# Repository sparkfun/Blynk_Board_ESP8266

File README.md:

SparkFun Blynk Board - ESP8266
========================================

[*SparkFun Blynk Board - ESP8266 (WRL-13794)*](https://www.sparkfun.com/products/13794)

The SparkFun Blynk Board is specially designed to work with the [Blynk mobile app](http://blynk.cc), for iOS or Android devices. Combining the Blynk Board with the Blynk app, you'll be able to easily complete a variety of Internet-of-Things (IoT) based projects: control LEDs from your phone! Wire up a door switch and receive phone notifications when it opens or closes. Plug a soil moisture sensor into a plant, and have it tweet at you when it's thirsty!

All of these projects - and more! - are pre-loaded into the Blynk Board. All you have to do is provision it (using the Blynk app), and start tinkering!

Repository Contents
-------------------

* **/Firmware** - Blynk Board core firmware and example code.
* **/Hardware** - Eagle design files (.brd, .sch)
* **/Production** - Production panel files (.brd)

Documentation
--------------
* **[Getting Started Guide](https://learn.sparkfun.com/tutorials/getting-started-with-the-sparkfun-blynk-board)** - Learn how to connect your Blynk Board to Wi-Fi, and start Blynking!
* **[Blynk Board Project Guide](https://learn.sparkfun.com/tutorials/blynk-board-project-guide/introduction)** - Explore over a dozen Blynk projects pre-loaded into the Blynk Board.
* **[Blynk Board Arduino Development Guide](https://learn.sparkfun.com/tutorials/blynk-board-arduino-development-guide)** - Learn how to begin programming the Blynk Board using Arduino, so you can create projects of your own!
* **[SparkFun Graphical Datasheets](https://github.com/sparkfun/Graphical_Datasheets/tree/master/Datasheets/ESP8266/BlynkBoard)** -Graphical Datasheets for the SparkFun Blynk Board.

Product Versions
----------------
* [SparkFun Blynk Board - ESP8266 (v1.0) (WRL-13794)](https://www.sparkfun.com/products/13794)- Initial release of the SparkFun Blynk Board - ESP8266.
* IoT Starter Kit with Blynk Board
  * [(KIT-14682)](https://www.sparkfun.com/products/14682) - Updated parts kit with thicker resistor leads.
  * [(KIT-13865)](https://www.sparkfun.com/products/13865) - A parts kit including the SparkFun Blynk Board.

Version History
---------------
* [HW v1.0, FW v1.0.3](https://github.com/sparkfun/Blynk_Board_ESP8266/releases/tag/HW_v1.0-FW_v1.0.3) - Minor update for ESP8266 Community board add on (v2.6.0 and above) when using interrupts.
* [HW v1.0, FW v1.0.2](https://github.com/sparkfun/Blynk_Board_ESP8266/releases/tag/HW_v1.0-FW_v1.0.2) - Initial release of the SparkFun Blynk Board hardware and firmware.

License Information
-------------------

This product is _**open source**_! 

Please review the LICENSE.md file for license information. 

If you have any questions or concerns on licensing, please contact technical support on our [SparkFun forums](https://forum.sparkfun.com/viewforum.php?f=152).

Distributed as-is; no warranty is given.

- Your friends at SparkFun.

_<COLLABORATION CREDIT>_

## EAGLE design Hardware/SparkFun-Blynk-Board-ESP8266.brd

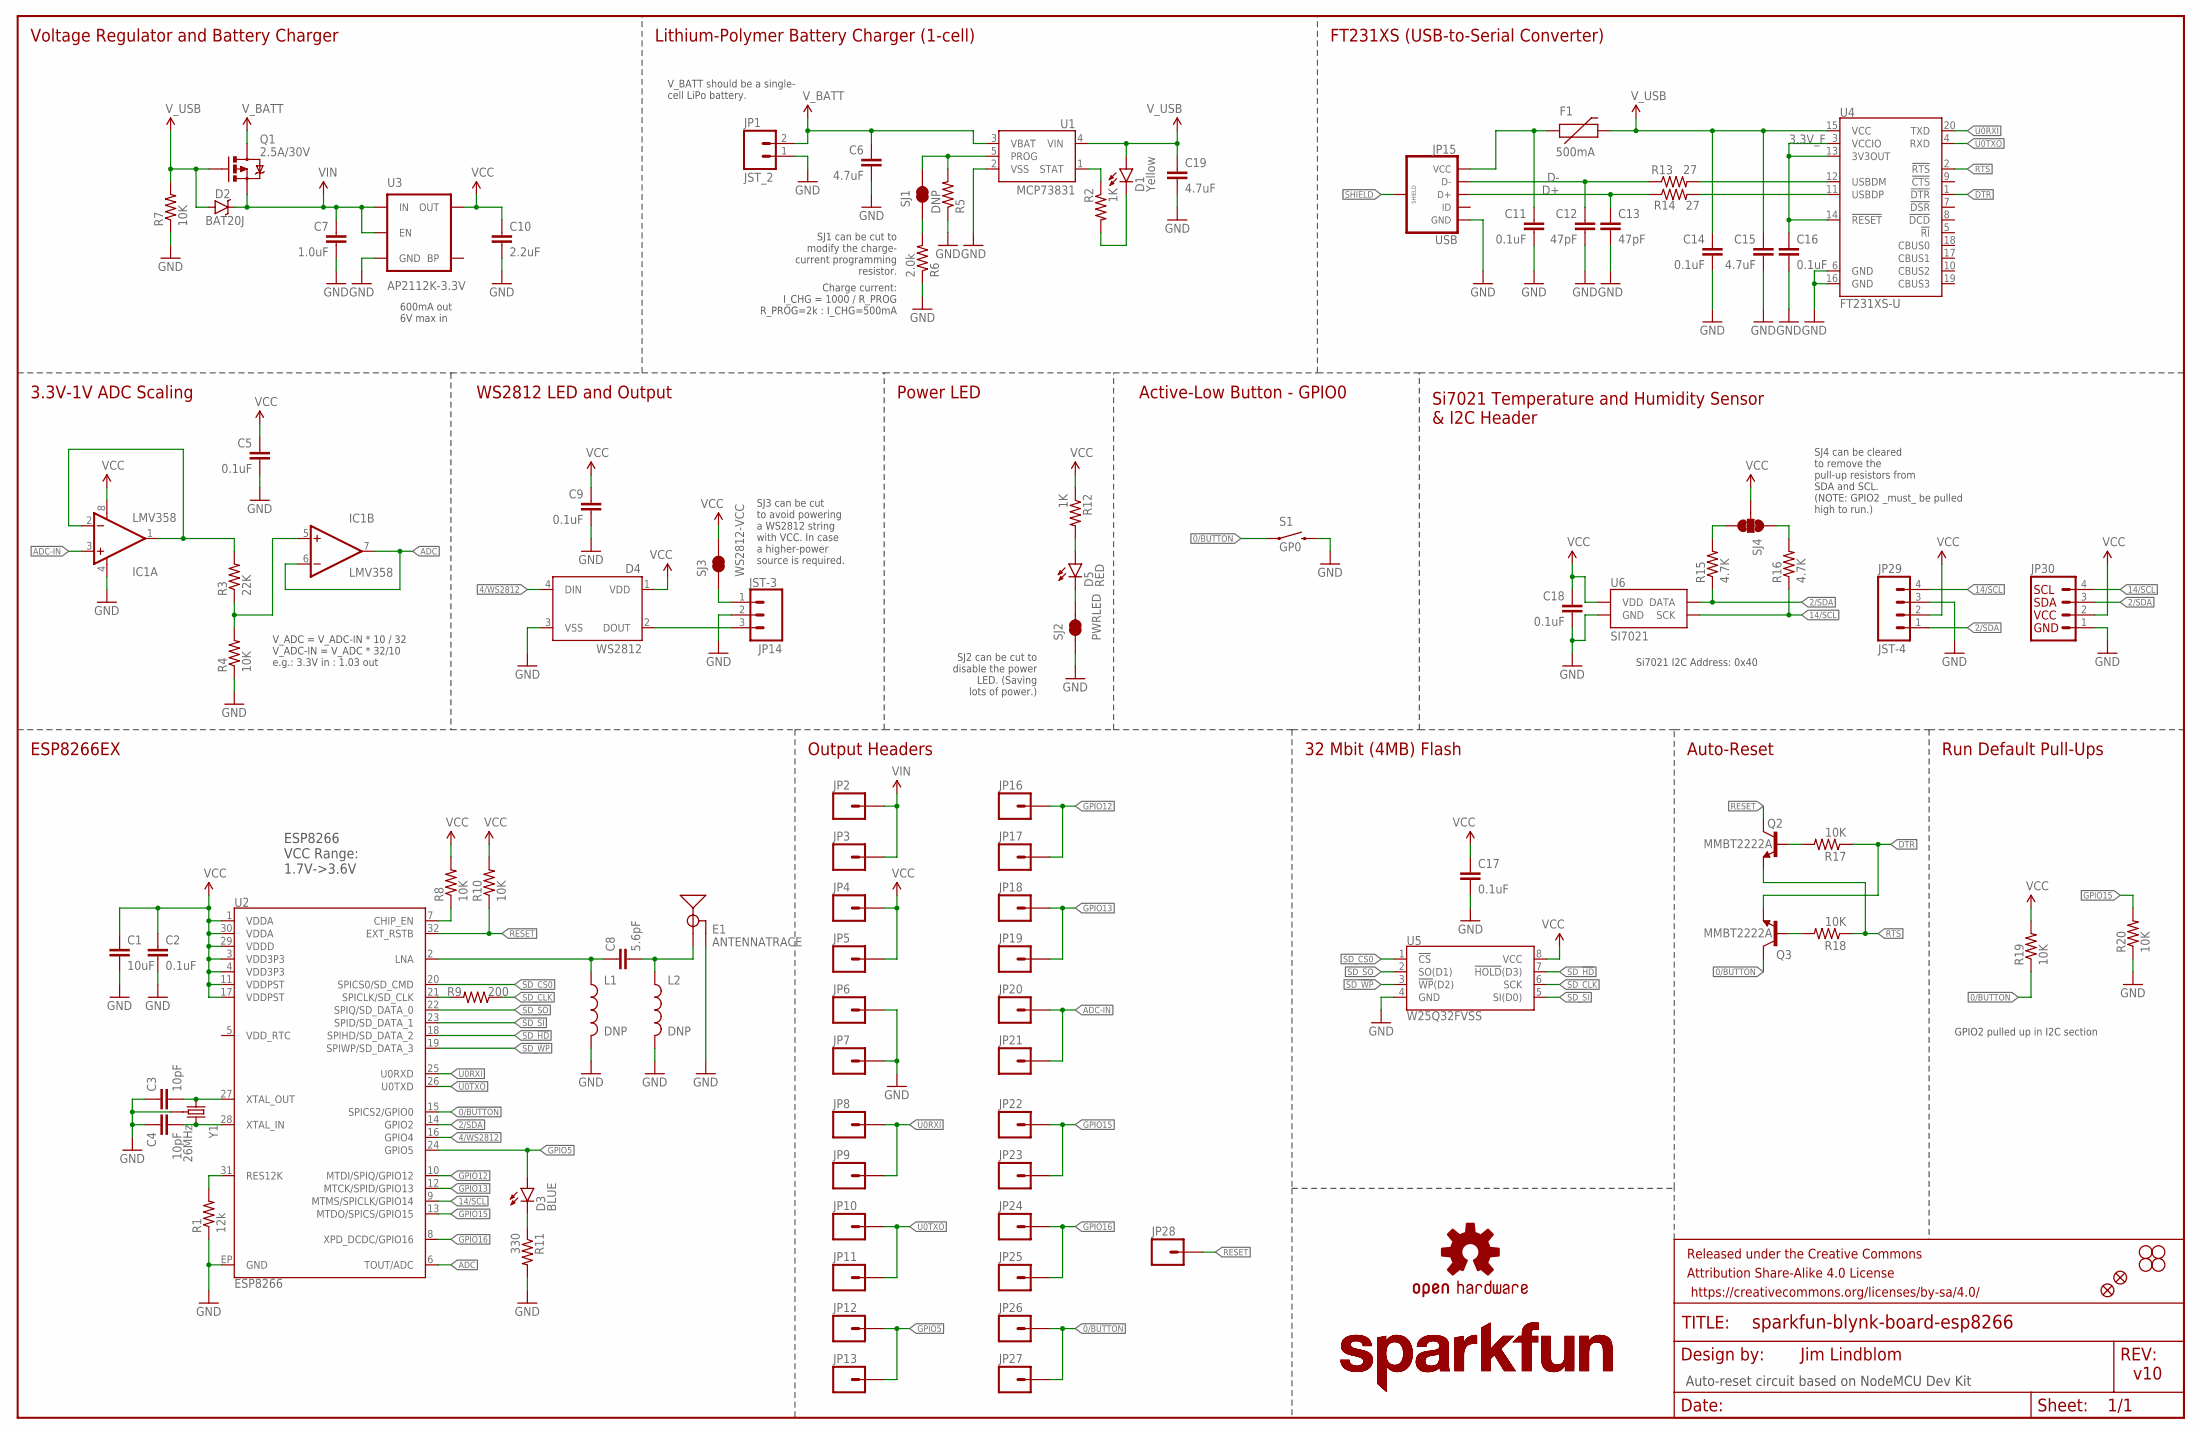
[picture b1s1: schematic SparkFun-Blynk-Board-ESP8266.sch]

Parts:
C1: 10uF; 0603-CAP
C2, C5, C9, C11, C14, C16, C17, C18: 0.1uF; 0603-CAP
C3, C4: 10pF; 0603-CAP
C6, C15, C19: 4.7uF; 0603-CAP
C7: 1.0uF; 0805-CAP
C8: 5.6pF; 0603-CAP
C10: 2.2uF; 0603-CAP
C12, C13: 47pF; 0603-CAP
D1: Yellow; LED-0603
D2: BAT20J; SOD-323
D3: BLUE; LED-0603
D4: WS2812; WS2812B
D5: RED; LED-0603
E1: ANTENNATRACE; TRACE_ANTENNA_2.4GHZ_25.7MM
F1: 500mA; PTC-1206
FID1, FID2: FIDUCIAL1X2; FIDUCIAL-1X2
FRAME1: FRAME-LEDGER; CREATIVE_COMMONS
IC1: LMV358; SO08
JP1: JST_2; JST-2-PTH
JP2, JP4, JP6, JP8, JP10, JP12, JP16, JP18, JP20, JP22, JP24, JP26: DNP; 1X01_ALLIGATOR_3MM_HALF
JP3, JP5, JP7, JP9, JP11, JP13, JP17, JP19, JP21, JP23, JP25, JP27, JP28: DNP; 1X01_NO_SILK
JP14: JST-3; JST-3-PTH-VERT
JP15: USB; USB-B-MICRO-SMD_V03
JP29: JST-4; JST-4-PTH-VERT
JP30: DNP; 1X04_NO_SILK
L1, L2: DNP; 0603
LOGO1: SFE_LOGO_NAME.2_INCH; SFE_LOGO_NAME_.2
LOGO2: OSHW-LOGOS; OSHW-LOGO-S
LOGO3: SFE_LOGO_NAME.3_INCH; SFE_LOGO_NAME_.3
Q1: 2.5A/30V; SOT23-3
Q2, Q3: MMBT2222A; SOT23-3@1
R1: 12k; 0603-RES
R2, R12: 1K; 0603-RES
R3: 22K; 0603-RES
R4: 10K; 0603-RES
R5: DNP; 1/6W-RES
R6: 2.0k; 0603-RES
R7, R8, R10, R17, R18, R19, R20: 10K; 0603-RES@1
R9: 200; 0603-RES
R11: 330; 0603-RES
R13, R14: 27; 0603-RES
R15, R16: 4.7K; 0603-RES
S1: GP0; TACTILE-SWITCH-SMD
SJ1: DNP; PAD-JUMPER-2-NC_BY_TRACE_YES_SILK
SJ2: PWRLED; PAD-JUMPER-2-NC_BY_TRACE_YES_SILK
SJ3: WS2812-VCC; PAD-JUMPER-2-NC_BY_TRACE_YES_SILK
SJ4: DNP; PAD-JUMPER-3-3OF3_NC_BY_TRACE_YES_SILK_FULL_BOX
STANDOFF1, STANDOFF2, STANDOFF3, STANDOFF4: STAND-OFF
U1: MCP73831; SOT23-5
U2: ESP8266; QFN32
U3: AP2112K-3.3V; SOT23-5
U4: FT231XS-U; SSOP20_L
U5: W25Q32FVSS; SOIC-8
U6: SI7021
Y1: 26MHz; CRYSTAL-SMD-3.2X2.5

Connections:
0/BUTTON: JP26.1@2, JP27.1, Q3.3 (C), R19.1, S1.1, S1.2 (1), U2.15 (SPICS2/GPIO0)
2/SDA: JP29.1, JP30.3, R15.1, U2.14 (GPIO2), U6.DATA
3.3V_F: C16.1, U4.3 (VCCIO), U4.13 (3V3OUT), U4.14 (!RESET)
4/WS2812: D4.4 (DIN), U2.16 (GPIO4)
14/SCL: JP29.4, JP30.4, R16.1, U2.9 (MTMS/SPICLK/GPIO14), U6.SCK
ADC: IC1.6 (-IN), IC1.7 (OUT), U2.6 (TOUT/ADC)
ADC-IN: IC1.3 (+IN), JP20.1@2, JP21.1
CHIP_EN: R8.1, U2.7 (CHIP_EN)
D+: C13.1, JP15.D+, R14.1
D-: C12.1, JP15.D-, R13.1
DTR: Q3.2 (E), R17.1, U4.1 (!DTR)
GND: C1.2, C2.2, C3.1, C4.1, C5.2, C6.2, C7.2, C9.2, C10.2, C11.2, C12.2, C13.2, C14.2, C15.2, C16.2, C17.2, C18.2, C19.2, D4.3 (VSS), E1.GND, E1.GND2 (GND), IC1.4 (V-), JP1.1, JP6.1@2, JP7.1, JP14.2, JP15.GND, JP29.3, JP30.1, L1.2, L2.2, R1.1, R4.1, R5.1, R6.1, R7.1, R11.2, R20.1, S1.3 (2), S1.4 (2), SJ2.1, U1.2 (VSS), U2.EP (GND), U3.2 (GND), U4.6 (GND), U4.16 (GND), U5.4 (GND), U6.GND, Y1.2 (GND), Y1.4 (GND)
GPIO5: D3.A, JP12.1@2, JP13.1, U2.24 (GPIO5)
GPIO12: JP16.1@2, JP17.1, U2.10 (MTDI/SPIQ/GPIO12)
GPIO13: JP18.1@2, JP19.1, U2.12 (MTCK/SPID/GPIO13)
GPIO15: JP22.1@2, JP23.1, R20.2, U2.13 (MTDO/SPICS/GPIO15)
GPIO16: JP24.1@2, JP25.1, U2.8 (XPD_DCDC/GPIO16)
LNA: C8.1, L1.1, U2.2 (LNA)
unnamed: R1.2, U2.31 (RES12K)
unnamed: C4.2, U2.28 (XTAL_IN), Y1.3 (2)
unnamed: C3.2, U2.27 (XTAL_OUT), Y1.1
unnamed: R13.2, U4.12 (USBDM)
unnamed: D5.C, SJ2.2
unnamed: Q2.1 (B), R17.2
unnamed: R14.2, U4.11 (USBDP)
unnamed: D3.C, R11.1
unnamed: R2.1, U1.1 (STAT)
unnamed: D5.A, R12.2
unnamed: R15.2, SJ4.3
unnamed: Q3.1 (B), R18.2
unnamed: R16.2, SJ4.1
unnamed: R5.2, SJ1.2, U1.5 (PROG)
unnamed: IC1.1 (OUT), IC1.2 (-IN), R3.2
unnamed: R6.2, SJ1.1
unnamed: D1.C, R2.2
unnamed: IC1.5 (+IN), R3.1, R4.2
unnamed: JP14.1, SJ3.1
RESET: JP28.1, Q2.3 (C), R10.1, U2.32 (EXT_RSTB)
RTS: Q2.2 (E), R18.1, U4.2 (!RTS)
SD_!HD!: U2.18 (SPIHD/SD_DATA_2), U5.7 (!HOLD!(D3))
SD_!WP!: U2.19 (SPIWP/SD_DATA_3), U5.3 (!WP!(D2))
SD_CLK: R9.1, U5.6 (SCK)
SD_CLK0: R9.2, U2.21 (SPICLK/SD_CLK)
SD_CS0: U2.20 (SPICS0/SD_CMD), U5.1 (!CS!)
SD_SI: U2.23 (SPID/SD_DATA_1), U5.5 (SI(D0))
SD_SO: U2.22 (SPIQ/SD_DATA_0), U5.2 (SO(D1))
SHIELD: JP15.SHIELD1 (SHIELD), JP15.SHIELD2 (SHIELD), JP15.SHIELD3 (SHIELD)
TRACE_ANT: C8.2, E1.ANT (SIGNAL), L2.1
U0RXI: JP8.1@2, JP9.1, U2.25 (U0RXD), U4.20 (TXD)
U0TXO: JP10.1@2, JP11.1, U2.26 (U0TXD), U4.4 (RXD)
VCC: C1.1, C2.1, C5.1, C9.1, C10.1, C17.1, C18.1, D4.1 (VDD), IC1.8 (V+), JP4.1@2, JP5.1, JP29.2, JP30.2, R8.2, R10.2, R12.1, R19.2, SJ3.2, SJ4.2, U2.1 (VDDA), U2.3 (VDD3P3), U2.4 (VDD3P3), U2.11 (VDDPST), U2.17 (VDDPST), U2.29 (VDDD), U2.30 (VDDA), U3.5 (OUT), U5.8 (VCC), U6.VDD
VIN: C7.1, D2.C, JP2.1@2, JP3.1, Q1.2 (S), U3.1 (IN), U3.3 (EN)
VUSB: C11.1, F1.1, JP15.VBUS (VCC)
V_BATT: C6.1, JP1.2, Q1.3 (D), U1.3 (VBAT)
V_USB: C14.1, C15.1, C19.1, D1.A, D2.A, F1.2, Q1.1 (G), R7.2, U1.4 (VIN), U4.15 (VCC)
WS2812-DOUT: D4.2 (DOUT), JP14.3

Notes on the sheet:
ESP8266EX
ESP8266 VCC Range: 1.7V->3.6V
FT231XS (USB-to-Serial Converter)
Auto-Reset
Run Default Pull-Ups
SJ2 can be cut to disable the power LED. (Saving lots of power.)
Jim Lindblom
v10
Auto-reset circuit based on NodeMCU Dev Kit
GPIO2 pulled up in I2C section
V_BATT should be a single- cell LiPo battery.
Charge current: I_CHG = 1000 / R_PROG R_PROG=2k : I_CHG=500mA
32 Mbit (4MB) Flash
Output Headers
3.3V-1V ADC Scaling
WS2812 LED and Output
Active-Low Button - GPIO0
Si7021 Temperature and Humidity Sensor & I2C Header
Voltage Regulator and Battery Charger
SJ1 can be cut to modify the charge- current programming resistor.
SJ4 can be cleared to remove the pull-up resistors from SDA and SCL. (NOTE: GPIO2 _must_ be pulled high to run.)
Si7021 I2C Address: 0x40
Lithium-Polymer Battery Charger (1-cell)
Power LED
SJ3 can be cut to avoid powering a WS2812 string with VCC. In case a higher-power source is required.
V_ADC = V_ADC-IN * 10 / 32 V_ADC-IN = V_ADC * 32/10 e.g.: 3.3V in : 1.03 out
600mA out 6V max in

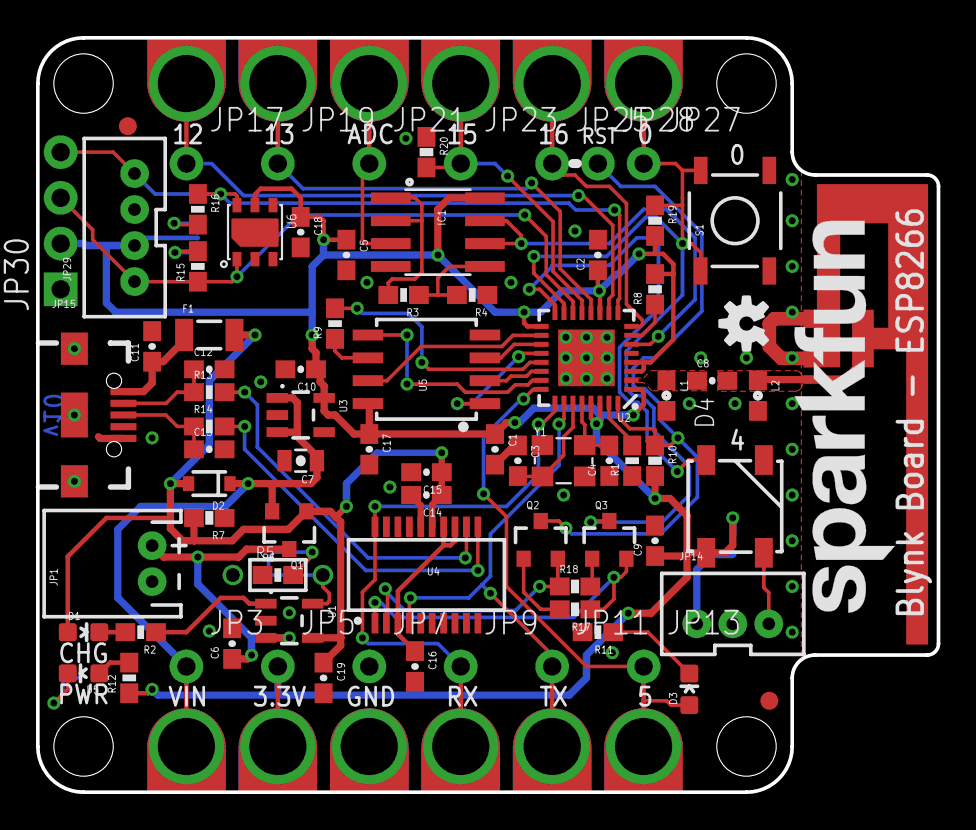
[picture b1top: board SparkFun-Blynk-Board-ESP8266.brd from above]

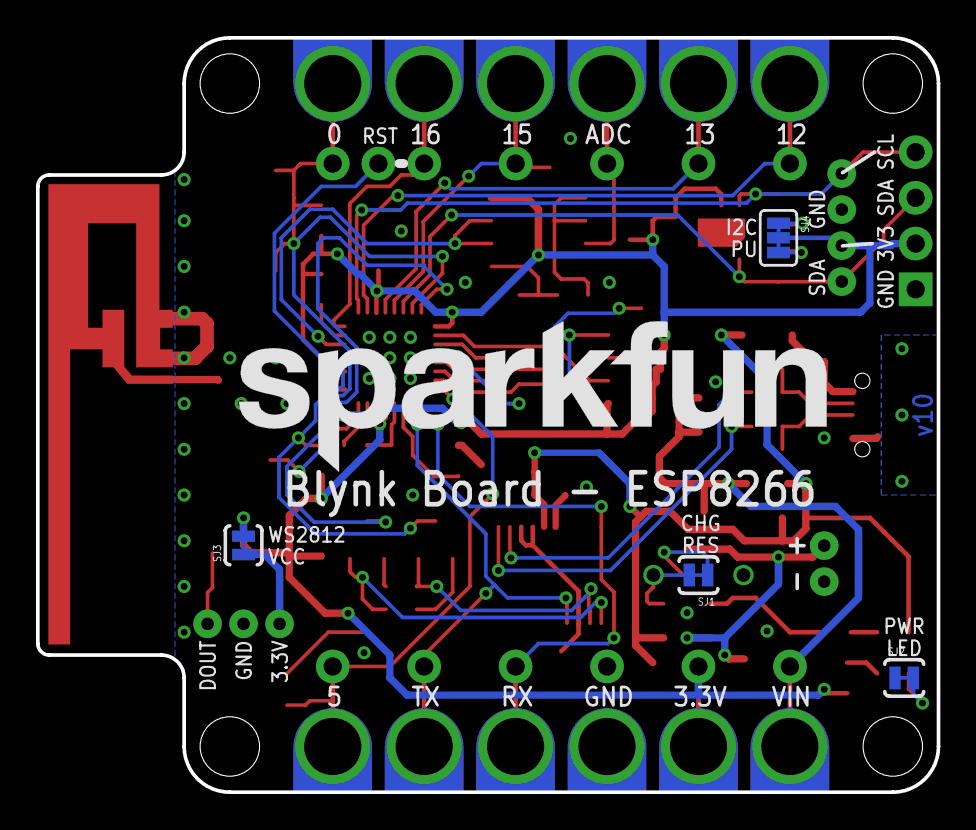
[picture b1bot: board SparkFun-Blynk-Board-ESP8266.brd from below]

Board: 2 copper layers, 50.0 x 41.9 mm, 104 parts (5 on the bottom side), 56 nets.

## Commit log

2016-01-08 Initial commit of hardware.
2016-01-11 Schematic cleanup
2016-01-11 Board cleanup
2016-01-11 Adding dimensions
2016-01-11 Adjsting board dimension to 0.01in grid
2016-01-11 Labeling battery connector.
2016-01-11 Re-configuring the I2C connector.
2016-01-11 Schematic cleanup, adding decoupling cap to batt charger
2016-01-12 Schematic clean-up and some PROD_ID's
2016-01-12 Adding PROD_ID's to U5 and JP14
2016-02-04 Moving WS2812-VCC jumper.
2016-02-04 Updating 32M Flash package.
2016-02-04 Fixing Op amp power supply.
2016-02-04 Fixing Si7021 tCream and tStop.
2016-02-05 Moving headers in to fit in breadboard.
2016-02-05 Upping version to v02
2016-02-05 Fixing board name silk
2016-02-05 Swapping JST connectors on I2C footprint.
2016-02-05 Silkscreen fixes
2016-02-05 Updating 4-pin JST PROD_ID
2016-02-05 created proto panel v02
2016-02-08 Updating board name on silkscreen.
2016-02-15 Changing file names to match product name.
2016-02-15 Moving some silk. Updating version number to v10.
2016-02-15 Fixing default layers.
2016-02-15 Moving PWR led a bit away from screwhead.
2016-02-15 Updating PROD_ID on JP29.
2016-02-15 created panel v10
2016-02-24 Initial commit of Blynk Board core firmware
2016-02-24 Adding custom libraries to README
2016-02-24 Generalizing debug statements.
2016-02-24 Adding serial WiFi config method.
2016-02-29 Adding board-selection info to readme.
2016-02-29 Filling out BlynkBoard demo experiments.
2016-03-01 Squash random exception(0) crashses
    - Changing Blynk.virtualWrite's of Strings to floats.
    - Fixing battery virtual variable names
2016-03-01 Adding runtime virtual variable to V30
2016-03-01 Cleaning up config mode process
    - Going comment-crazy on Core firmware
    - Adding MODE_WAIT_CONFIG - if WiFi or Blynk fail to connect on startup,
    press the GP0 button to re-enter config mode.
    - Adding support to break out of WiFi or Blynk connect using GP0 button
    - Merging WiFi and Blynk connect functionality into singular functions in
    BlynkBoard_Setup.ino
2016-03-02 Fixing startup bug - EEPROM defaults to 255.
2016-03-03 Fixing IP address print
2016-03-03 Cleaning up BlynkBoard Blynk Mode
    - Moving as many functions out of loop as possible
    - Updating virtual pin numbers to match experiment order
    - Adding Blynk demo functionality
2016-03-03 Cleaning up BlynkMode, fixing button-press bug
2016-03-03 More BlynkMode cleanup - joystick, push, email.
2016-03-04 recreated panel v10 for better routing
2016-03-04 Flushing after terminal prints.
2016-03-04 Fixing W25Q32FVSS footprint.
2016-03-04 Adding v10 top dimension pdf.
2016-03-07 Reverting button-checks back to polling. Running into debounce errors.
2016-03-07 Added empty directory for Bridge example
2016-03-08 Added code for two devices.
2016-03-08 Using Joystick Merge instead of split.
2016-03-09 Fixing open network connect in serial config & error connect at startup.
2016-03-09 Switching light updates to polling.
2016-03-09 Changing RGB colors - connect to blue, Blynk to Blynk green.
2016-03-09 Adding scrollbar select list to HTML config page.
2016-03-10 Adding scan option to serial config.
2016-03-10 Persistent SSID color codes through reset. Default to color code mode.
2016-03-10 Adding host/port input framework.
2016-03-10 Adding host/port selection to serial config.
2016-03-10 Fixing Blynk re-connect errors.
2016-03-11 Add board_info.json WebPage styling Sorting of webpage SSIDs
2016-03-11 Cleaned up
2016-03-11 Removed unused variable
2016-03-11 Removed old comment
2016-03-11 Adding button hold timer. Hold GP0 down for 3 seconds to re-enter config mode.
2016-03-11 Added headers to top of code with license and vrsion info
2016-03-11 Fixed up description in header
2016-03-11 Added content to the README file
2016-03-11 Making root page more responsive to low-res devices.
2016-03-11 Incrementing version number.
2016-03-11 Adding DNS server support to config mode. Beefing up config HTML response.
2016-03-14 Validate html and fix some labels
2016-03-14 Adding check to RGB. If invalid number of params, ESP8266 was crashing.
2016-03-14 Fixing reconnect errors, and 0.0.0.0 access point bug
2016-03-14 Allow resetting EEPROM using button in DEBUG mode
2016-03-14 Fix mobile webpage rendering
2016-03-15 CAPTIVE_PORTAL_ENABLE option back to life
2016-03-15 Adding framework for self-test, comment cleanup.
2016-03-15 Updating LCD splash screen
2016-03-15 Defaulting DNS server on
2016-03-15 Fixing Blynk connect timeout - was wayyy to long.
2016-03-15 Re-thinking Blynk connect timeout. Checking against millis.
2016-03-16 Oops, fixing Blynk timeout logic.
2016-03-16 Updating self-test routine.
2016-03-16 Modifying self-test exit.
2016-03-16 Adding adustable brightness to RGB LED.
2016-03-16 Adding periodic splashscreen updates, in case they're not caught in blynk connect
2016-03-17 Re-working twitter project.
2016-03-17 Adding check if came out of AP-setup-fail reset.
2016-03-17 Polishing twitter project.
2016-03-17 Polishing up BB_DEBUG and BB_PRINT statements.
2016-03-17 Re-working push project. Fixing default hostname in serial print.
2016-03-17 Cleaning up some compiler warnings - v1.0.0!
2016-03-17 Slight fix to self-test mode.
2016-03-17 Adding delay at start - else board's intermittently pop up as serial ballpoint mice :S
2016-03-25 UUpdating readme
2016-03-25 Adding a bit to readme.
2016-03-25 Fixing version release tag.
2016-03-25 Fixing Blynk Board in Arduino IDE readme text
2016-03-25 Readme typos
2016-03-25 Adding values to all parts
2016-03-25 Update Blynk library release
2016-03-25 Removing temporary library - all parts added to SparkFun libraries
2016-03-29 Adding value to 2-pin JST
2016-03-30 Adding laundry monitor firmware example.
2016-03-30 Updating Laundry Monitor example.
2016-03-31 Fixing timer display on LCD
2018-04-10 TYpo virutal -> virtual
2018-04-10 Comment experiment 9 servo wrong
    It is mentioned to use split mode V14,V15, but it should be merge mode V14
2019-01-23 Fixed SELF_TEST_ENABLED being defined
    By having SELF_TEST_ENABLED on line 29, the code enters the conditional statement on line 107, which will have it run a modified self-test function. According to line 112, and confirmed by multiple t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
2020-04-13 Adding a Requirement for ISR when using the ESP8266 Community Board Add-On
    The SparkFun Blynk board add-on is now supported by
    the ESP8266 Community! If you are installing the ESP8266
    board add-on v2.6.0+ and using an interrupt service routine,
    you must include `ICACHE_RAM_ATTR` before the function
    definition. This was a requirement after v2.5.1+. If users do not add this before the ISR, the examples will not run even though it can compile/upload via the Arduino IDE.
2020-04-13 Add Comment and "Update Firmware Number"
    - add comment about SELF_TEST_ENABLED
    - update firmware version number to distinguish the ones used with production and the ESP8266 Community's board file (v2.6.0 and above) which requires a `ICACHE_RAM_ATTR` to be placed before ISR defi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
    - overall, this should not affect the board's functionality when using it with the Blynk App
2020-04-13 Update README.md
    Update contact for support.
2020-04-13 Update README.md
    The SparkFun Blynk Board add is now supported by the [ESP8266 Community](https://github.com/esp8266/Arduino) as of v2.6.0! Updating to point to their board url.

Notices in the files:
parts and their libraries:
SparkFun-Capacitors: Licensing: Creative Commons ShareAlike 4.0 International - https://creativecommons.org/licenses/by-sa/4.0
SparkFun-Aesthetics: Released under the Creative Commons Attribution Share-Alike 4.0 License
SparkFun-Aesthetics: https://creativecommons.org/licenses/by-sa/4.0
